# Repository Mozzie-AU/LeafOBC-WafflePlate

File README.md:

# LeafOBC-WafflePlate

Reverse engineering the "waffle plate" power module from the **2012 Nissan Leaf on-board charger (OBC)**, with the goal of building a **functional replica from regular, off-the-shelf components**.

The original module is a hybrid power assembly. It is a single-sided copper circuit on a ceramic substrate, bonded to an aluminium base plate, and mounted in a moulded frame. When one fails, the charger is usually written off. A drop-in replacement made from discrete, readily available parts would let these chargers be repaired.

<p align="center">
  
  <br>
  <em>Top side of the waffle plate. The potting and each component's encapsulation have been removed by laser etching, exposing the bare dies, bond wires and copper tracks. Stitched from 21 microscope images (5320 × 4802 px). Click for full resolution, or see the <a href="images/annotated/component-map.jpg">annotated component map</a>.</em>
</p>

> ⚠️ **High voltage.** The OBC works from mains AC and charges a traction battery of several hundred volts DC. Capacitors in the charger can hold a lethal charge after it is disconnected. Anything in this repo is provided for documentation and research, with no warranty. See the licence.

## Status

| Stage | State |
|---|---|
| Imaging | ✅ Stitched (21 tiles, ~5300 × 4800 px). The bottom is a plain aluminium plate, so it isn't imaged |
| Connector pinout | ⬜ Not started |
| Component identification | 🟡 Main semiconductors and shunts located ([map](images/annotated/component-map.jpg)) |
| Circuit topology / schematic | 🟡 KiCad schematic: input bridge, shunt and output rectifier verified; PFC wired; full bridge first pass ([notes](docs/schematic-notes.md)) |
| Replica design | 🟡 Altium design by Angel Monera Martinez, built but untested ([hardware/replica-altium](hardware/replica-altium/)) |
| Bench test | ⬜ Not started |

## Repository layout

```
docs/              Notes, findings, component inventory, imaging method
images/raw/        Original microscope tiles, one folder per capture set
images/stitched/   Stitched mosaics
hardware/
  original-module/ KiCad schematic of the original module (reverse-engineered)
  replica-altium/  Altium replica design by Angel Monera Martinez, with fabrication outputs
tools/stitch/      Script that stitches microscope tiles into a mosaic
```

## Documents

- [Overview and open questions](docs/overview.md)
- [Schematic notes and verification checklist](docs/schematic-notes.md)
- [PFC gate driver: original pin-out and replica wiring error](docs/pfc-gate-driver.md)
- [Primary full bridge: gate network (work in progress)](docs/full-bridge-gate-drive.md)
- [Component inventory](docs/component-inventory.md)
- [Imaging and stitching method](docs/imaging.md)
- [Altium replica build log (Angel Monera Martinez)](docs/replica-altium-notes.md)
- [External references](docs/references.md): the Ukrainian schematic (module CZ1525RPWR012) and forum threads

## Contributors

- **Ray (Mozzie-AU)**: reverse engineering, imaging, meter verification, repository
- **Angel Monera Martinez**: Altium replica design and build log ([hardware/replica-altium](hardware/replica-altium/)), contributed with permission

## Contributing

Information from anyone who has worked on Leaf (ZE0) chargers is very welcome. This includes failure modes, part markings, service documents and photos. Please open an issue or pull request.

## Licence

Hardware designs and documentation are released under the **CERN Open Hardware Licence v2 – Strongly Reciprocal** ([CERN-OHL-S-2.0](LICENSE)).

The Altium replica design in `hardware/replica-altium/` and its build log are the work of Angel Monera Martinez, included with his permission.

Nissan and Leaf are trademarks of Nissan Motor Co., Ltd. This project is independent and is not affiliated with or endorsed by Nissan.

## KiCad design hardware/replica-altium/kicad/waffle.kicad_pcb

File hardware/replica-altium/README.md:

# Altium replica design (Angel Monera Martinez)

A drop-in replacement for the waffle plate built from off-the-shelf packaged parts on a two-layer PCB. **Designed by Angel Monera Martinez** and included here with his permission. His build log is in [`docs/replica-altium-notes.md`](../../docs/replica-altium-notes.md).

> **Status: untested.** Angel assembled a board into a charger in January 2025, but it had not been run when these files were shared.

The power semiconductors sit on the underside, against the charger's cooling plate. The gate drive and other small parts are on the top.

## Contents

| Path | What |
|---|---|
| `altium/Nissan Leaf Waffle.PrjPcb` | Altium project |
| `altium/waffle.SchDoc` | Main schematic |
| `altium/igbt pair.SchDoc` | Sub-sheet: one switch (IGBT pair plus gate network), repeated four times for the full bridge (designators suffixed NE/NW/SE/SW) |
| `altium/waffle.PcbDoc`, `altium/waffle.PcbLib` | PCB and footprint library |
| `altium/Nissan Leaf Waffle.SCHLIB` | Schematic symbol library |
| `altium/waffer.OutJob` | Output job used to produce the fabrication files |
| `fabrication/2024-10-28-jlcpcb/` | Gerbers, NC drill, BOM, pick and place, DRC and stack-up reports **for the 27 Oct 2024 version** (the one sent to JLCPCB) |
| `kicad/` | **KiCad conversion** of the 4 Dec version (schematic, PCB, symbol library, schematic PDF). See below |
| `renders/` | 3D renders of the board |

## Versions (git history)

| Date | Commit message | Change |
|---|---|---|
| 2024-10-27 | *Add Angel Monera Martinez's Altium replica design* | Version sent to JLCPCB, with fabrication outputs |
| 2024-11-23 | *Replica design: 23 Nov 2024 version* | Enlarged IGBT and diode pads (PCB only) |
| 2024-12-04 | *Replica design: 4 Dec 2024 version* | Adds snap-off support PCBs that hold the pins while soldering. Schematic and PCB updated. Current files |

Use `git log -- hardware/replica-altium/altium/waffle.PcbDoc` to step through them.

**Not included:** after the January 2025 test fit, Angel moved the pins on one side 1.5 mm outward and corrected the mounting holes, which are not square. That revision was not in the shared files. Ask Angel for it before ordering boards.

**The fabrication outputs are out of date.** They match the 27 Oct version, not the current files. Regenerate them from the OutJob before ordering.

## Bill of materials (from the 27 Oct fabrication BOM)

| Qty | Part | Designators | Function |
|---|---|---|---|
| 11 | HGT1S10N120BNST (BOM footprint: PG-TO252-3) | Q3–Q5, Q6/Q7 × NE/NW/SE/SW | PFC switches (3) and full bridge (8) |
| 20 | SE20DLJ-M3/I (BOM footprint: PG-TO252-3) | D1–D20 | Input bridge, boost, freewheel and output rectifier diodes |
| 1 | BCX53-16 (PNP, SOT-89) | Q1 | PFC gate driver |
| 1 | BCX56-16 (NPN, SOT-89) | Q2 | PFC gate driver |
| 2 | 1 mΩ 1206 | R1, R9 | Current shunts |
| 2 | 100 k NTC (NB20N50104JBA) | R4, R8 | Temperature sensing |
| 3 | 39 Ω | R5–R7 | PFC gate resistors |
| 12 | 10 Ω | R10–R12 × NE/NW/SE/SW | Full-bridge gate resistors |
| 4 | 1 kΩ | R13 × NE/NW/SE/SW | Gate–emitter resistors |
| 8 | 1 nF | C2, C3 × NE/NW/SE/SW | Gate capacitors |
| 1 | 10 kΩ | R2 | |
| 1 | 43 Ω | R3 | |
| 1 | 1 µF | C1 | |

Inconsistencies to check:

- **PFC gate driver wired wrongly:** Q1 (BCX53) and Q2 (BCX56) have emitter and collector swapped, so the push-pull stage can't drive the PFC gates. See [docs/pfc-gate-driver.md](../../docs/pfc-gate-driver.md) for the original wiring and the fix.

- Angel's notes name **IGD08N120S7** IGBTs and **STTH25M06B** diodes, but the BOM lists HGT1S10N120BNST and SE20DLJ-M3/I. Confirm with Angel which parts he actually fitted.
- The diode line's supplier part numbers (VS-E5TX3012S2L-M3) don't match the part named in the same line (SE20DLJ-M3/I).
- The IGBT line's description reads "IGBT N type 20A(40) 600V dpak, possible replacement STB27NM60N", which doesn't match the HGT1S10N120BNST part name.

## Opening the files

- **Altium Designer:** open `Nissan Leaf Waffle.PrjPcb` in `altium/`.
- **KiCad 7 or later:** open `kicad/waffle.kicad_pro`.

## KiCad version (`kicad/`)

The Altium files (4 Dec 2024 version) were converted with KiCad 7.0.11's own Altium importers:

- **Schematic:** *File → Import → Non-KiCad Schematic* on `waffle.SchDoc`, which pulls in the `igbt pair` sub-sheet.
- **PCB:** the same importer, run through KiCad's Python API on `waffle.PcbDoc`.

| File | What |
|---|---|
| `waffle.kicad_pro` | Project |
| `waffle.kicad_sch` | Main sheet |
| `igbt pair.kicad_sch` | Switch sub-sheet, used four times (NW, NE, SW, SE) |
| `waffle-altium-import.kicad_sym`, `sym-lib-table` | Symbols extracted from the Altium design |
| `waffle.kicad_pcb` | PCB (footprints are embedded in the board) |
| `ALTIUM_EMBEDDED_MODELS/` | 3D model carried over from the PcbDoc |
| `waffle-schematic.pdf` | PDF of the schematic |

**One fix was made after import.** Altium's multichannel naming (NE/NW/SE/SW suffixes on the four copies of the switch sheet) didn't survive the import. All four copies came in with identical names (Q6, R10 and so on), which in KiCad merges the four switches' gate nets into one. Each sheet copy was given its Altium channel name (`igbt pair NE` and so on), confirmed from the sheet-symbol records in the `.SchDoc`. Each part was given its per-channel reference (`Q6NE`, `R10SW` and so on), matching the PCB.

**Checks made on the conversion:**

- The schematic netlist and the PCB connectivity were compared pin by pin. All 219 pins the two have in common group into the same 42 nets, so the conversion didn't change any connectivity.
- The schematic has one extra part, **J2**, a second 72-pin edge-connector symbol with no footprint on the board. It came across from the Altium schematic as-is.
- The PCB has 312 footprints in total. Only 68 of them are named parts; the rest are the pins and the snap-off support boards.

**Known quirks:**

- KiCad warns about *annotation errors* when exporting. The only cause is the Altium-style names that end in letters (`Q6NE`). KiCad expects names to end in a number. It's cosmetic, and the names are kept so they match the PCB, the BOM and Angel's notes. **Don't run *Annotate Schematic*** unless you mean to rename these parts. If you do, update the PCB with *Tools → Update PCB from Schematic* and tick *Re-link footprints to schematic symbols based on their reference designators*.
- The schematic and PCB were imported separately, so the footprints are not yet linked to the symbols. The first *Update PCB from Schematic* should use the same re-link option.
- The PCB import gave 271 warnings. All of them say items on Altium mechanical layers 71 and 72, which have no KiCad equivalent, were moved to `Eco1_User`.
- The ERC and DRC rules have not been tuned for KiCad. Treat their first results as a to-do list, not as design errors.

## Relation to the reverse-engineered schematic

[`../original-module/`](../original-module/) is our schematic of the **original** module. Angel's netlist is an independent reading of the same circuit, so the two can be cross-checked. Any difference is worth a meter check on the original module.

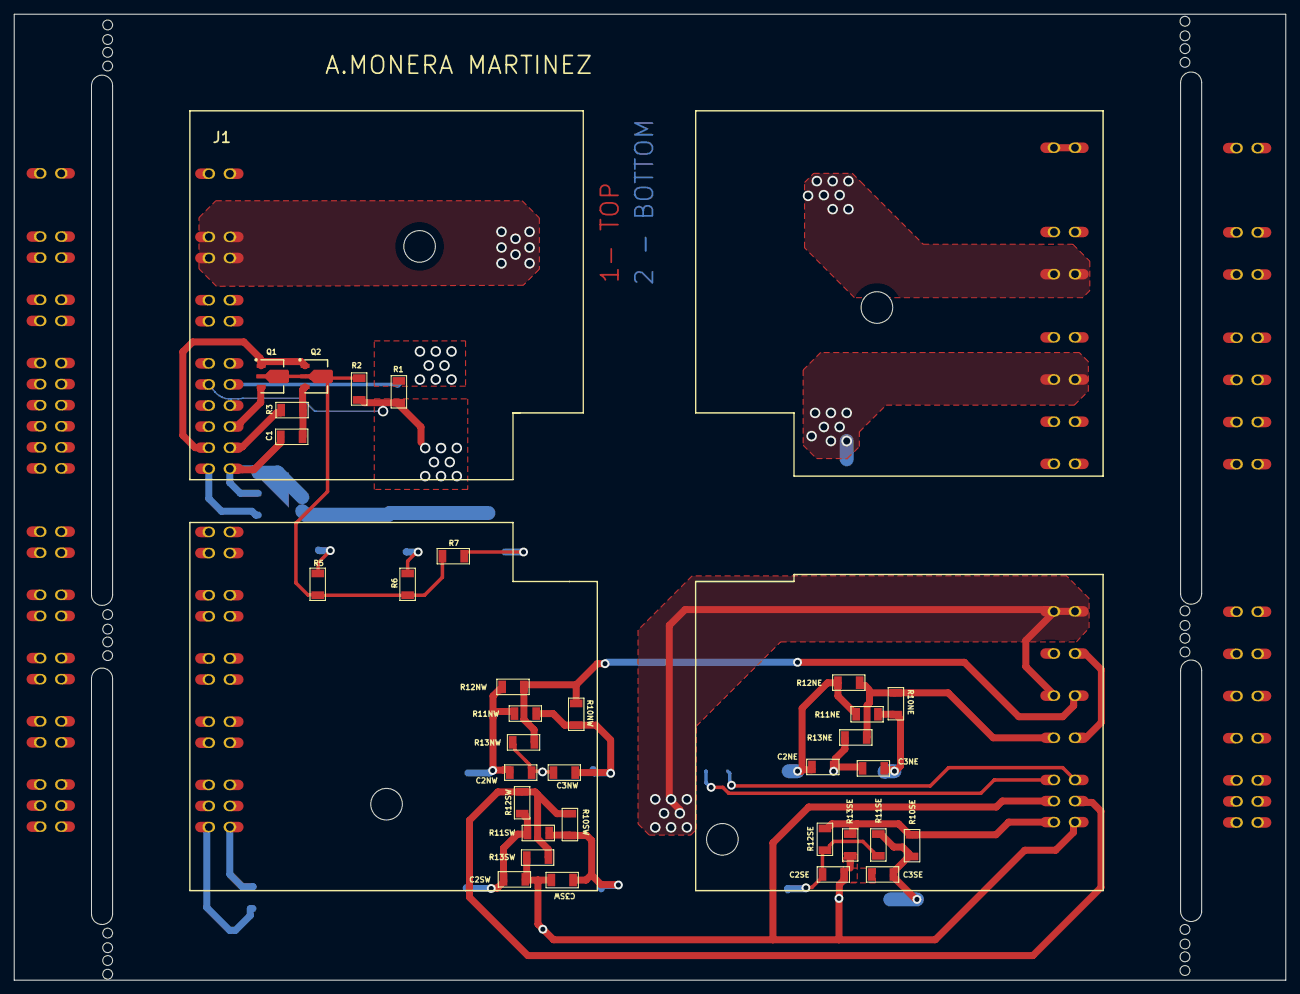
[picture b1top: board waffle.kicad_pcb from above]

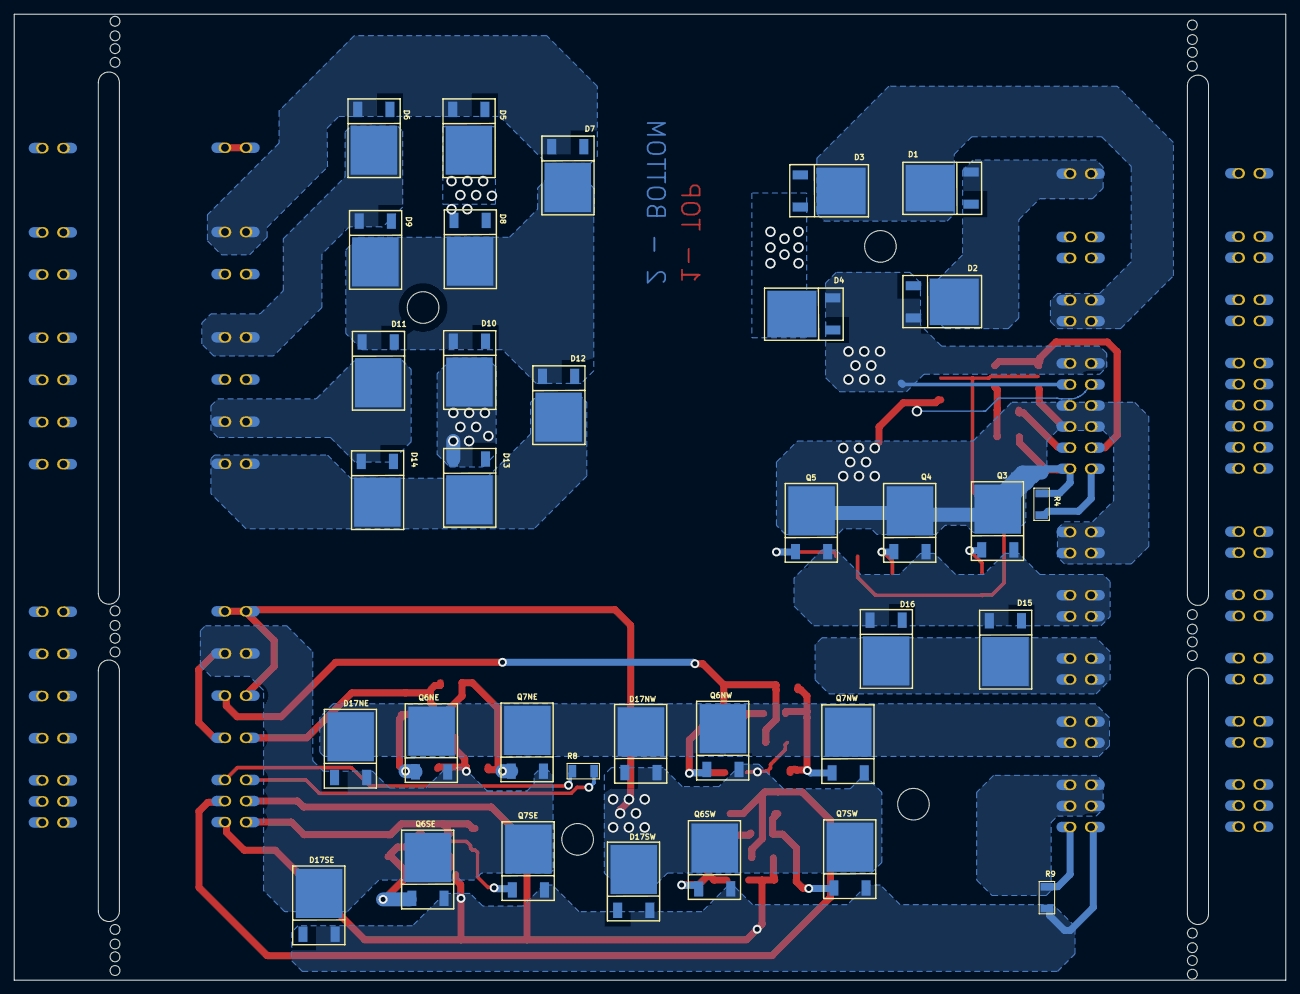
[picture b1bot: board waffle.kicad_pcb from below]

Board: 2 copper layers, 181.0 x 137.5 mm, 68 parts (34 on the bottom side), 42 nets.

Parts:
C1: 1uf; 1206
C2NE, C2NW, C2SE, C2SW, C3NE, C3NW, C3SE, C3SW: 1nF; 1206
D1, D2, D3, D4, D5, D6, D7, D8, D9, D10, D11, D12, D13, D14, D15, D16, D17NE, D17NW, D17SE, D17SW: SE20DLJ-M3/I; PG-TO252-3 - DIODE
J1: connector_waffle; WAFFLE
Q1: BCX53-16; SOT-89
Q2: BCX56-16; SOT-89
Q3, Q4, Q5, Q6NE, Q6NW, Q6SE, Q6SW, Q7NE, Q7NW, Q7SE, Q7SW: HGT1S10N120BNST; PG-TO252-3
R1, R9: 1mOHM; 1206
R2: 10K; 1206
R3: 43R; 1206
R4, R8: NB20N50104JBA; 1206
R5, R6, R7: 39R; 1206
R10NE, R10NW, R10SE, R10SW, R11NE, R11NW, R11SE, R11SW, R12NE, R12NW, R12SE, R12SW: 10R; 1206
R13NE, R13NW, R13SE, R13SW: 1K; 1206

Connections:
GND: J1.45, J1.46
L2: D15.A, D16.A, J1.27, J1.28, J1.29, J1.30, Q3.2, Q4.2, Q5.2
N0A: D5.A, D6.A, D7.A, J1.47, J1.48
N1: C1.2, J1.13, J1.15, J1.16, J1.17, J1.18, J1.22, J1.23, J1.24, J1.25, J1.26, Q1.3, Q3.3, Q4.3, Q5.3, R1.1, R2.2, R4.2
N-N1: J1.39, J1.40, J1.41, J1.42, J1.44, R9.2
N-N1_SHUNT: C2SE.2, C2SW.2, C3SE.2, C3SW.2, D17SE.A, D17SW.A, J1.43, J1.69, J1.72, Q6SE.2, Q6SW.2, Q7SE.2, Q7SW.2, R9.1, R13SE.1, R13SW.1
NetC1_1: C1.1, Q2.3, R3.2
NetC2NE_1: C2NE.1, Q7NE.1, R11NE.1, R12NE.2
NetC2NW_1: C2NW.1, Q7NW.1, R11NW.1, R12NW.2
NetC2SE_1: C2SE.1, Q7SE.1, R11SE.1, R12SE.2
NetC2SW_1: C2SW.1, Q7SW.1, R11SW.1, R12SW.2
NetC3NE_1: C3NE.1, Q6NE.1, R10NE.2, R11NE.2
NetC3NW_1: C3NW.1, Q6NW.1, R10NW.2, R11NW.2
NetC3SE_1: C3SE.1, Q6SE.1, R10SE.2, R11SE.2
NetC3SW_1: C3SW.1, Q6SW.1, R10SW.2, R11SW.2
NetD1_A: D1.A, D2.K, J1.1, J1.2
NetD1_K: D1.K, D3.K, J1.7, J1.8, J1.9, J1.10
NetD2_A: D2.A, D4.A, J1.11, J1.12, J1.14, R1.2
NetD3_A: D3.A, D4.K, J1.3, J1.4, J1.5, J1.6
NetD7_K: D7.K, D8.K, D9.K, D10.A, D11.A, D12.A
NetJ1_19: J1.19, Q1.1, Q2.1
NetJ1_20: J1.20, R3.1
NetJ1_21: J1.21, R4.1
NetJ1_64: J1.64, R10NW.1, R12NW.1, R13NW.2
NetJ1_65: J1.65, R10NE.1, R12NE.1, R13NE.2
NetJ1_67: J1.67, R8.1
NetJ1_68: J1.68, R8.2
NetJ1_70: J1.70, R10SW.1, R12SW.1, R13SW.2
NetJ1_71: J1.71, R10SE.1, R12SE.1, R13SE.2
NetQ1_2: Q1.2, Q2.2, R2.1, R5.2, R6.2, R7.2
NetQ3_1: Q3.1, R5.1
NetQ4_1: Q4.1, R6.1
NetQ5_1: Q5.1, R7.1
P0A: D12.K, D13.K, D14.K, J1.57, J1.58
T1A: C2NW.2, C3NW.2, D17NW.A, D17SW.K, J1.59, J1.60, J1.63, Q6NW.2, Q6SW.3, Q7NW.2, Q7SW.3, R13NW.1
T4A: C2NE.2, C3NE.2, D17NE.A, D17SE.K, J1.61, J1.62, J1.66, Q6NE.2, Q6SE.3, Q7NE.2, Q7SE.3, R13NE.1
T5A: D11.K, D14.A, J1.55, J1.56
T6A: D10.K, D13.A, J1.53, J1.54
T7A: D5.K, D8.A, J1.49, J1.50
T8A: D6.K, D9.A, J1.51, J1.52
p: D17NE.K, D17NW.K, J1.35, J1.36, J1.37, J1.38, Q6NE.3, Q6NW.3, Q7NE.3, Q7NW.3
p1: D15.K, D16.K, J1.31, J1.32, J1.33, J1.34
